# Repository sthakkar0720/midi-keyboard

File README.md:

# midi-keyboard
<h1>A custom MIDI keypad with slides, switches, rotary encoders, and capacitive touch. Built with the Hack Club Half Life guide.</h1>
I chose to make this because it is a music device and that is cool and it is one more cool piece of tech to put on my desk by my laptop. It provides accessibility for mixing my own music and I am hoping it works with spotify!

## I will be funding this project myself! This is NOT incomplete.

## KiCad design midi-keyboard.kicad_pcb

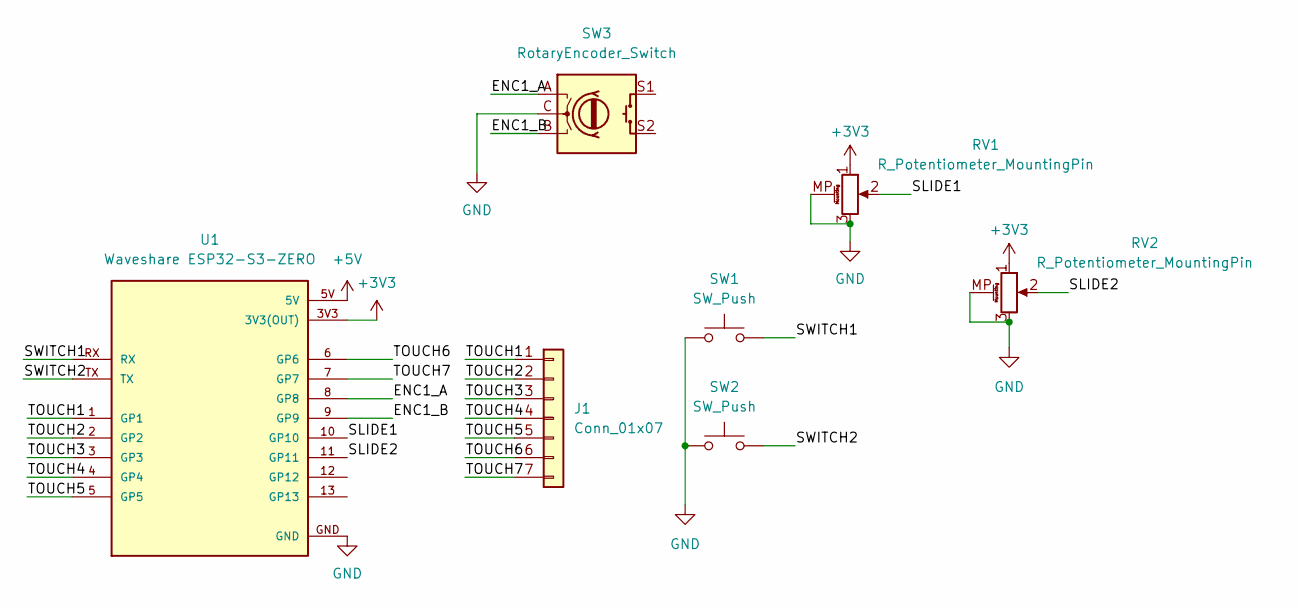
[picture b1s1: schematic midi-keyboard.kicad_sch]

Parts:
J1: Conn_01x07; Capacitative_7_Touch
RV1, RV2: R_Potentiometer_MountingPin; Potentiometer_Bourns_PTA1543_Single_Slide
SW1, SW2: SW_Push; Kailh Choc Low-Profile Switches
SW3: RotaryEncoder_Switch; RotaryEncoder_Alps_EC11E-Switch_Vertical_H20mm
U1: Waveshare ESP32-S3-ZERO; Waveshare ESP32-S3-Zero; PARTREV NA

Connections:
+3V3: RV1.1, RV2.1, U1.3V3 (3V3(OUT))
+5V: U1.5V
/ENC1_A: SW3.A, U1.8 (GP8)
/ENC1_B: SW3.B, U1.9 (GP9)
/SLIDE1: RV1.2, U1.10 (GP10)
/SLIDE2: RV2.2, U1.11 (GP11)
/SWITCH1: SW1.2, U1.RX
/SWITCH2: SW2.2, U1.TX
/TOUCH1: J1.1, U1.1 (GP1)
/TOUCH2: J1.2, U1.2 (GP2)
/TOUCH3: J1.3, U1.3 (GP3)
/TOUCH4: J1.4, U1.4 (GP4)
/TOUCH5: J1.5, U1.5 (GP5)
/TOUCH6: J1.6, U1.6 (GP6)
/TOUCH7: J1.7, U1.7 (GP7)
GND: RV1.3, RV1.MP (MountPin), RV2.3, RV2.MP (MountPin), SW1.1, SW2.1, SW3.C, U1.GND

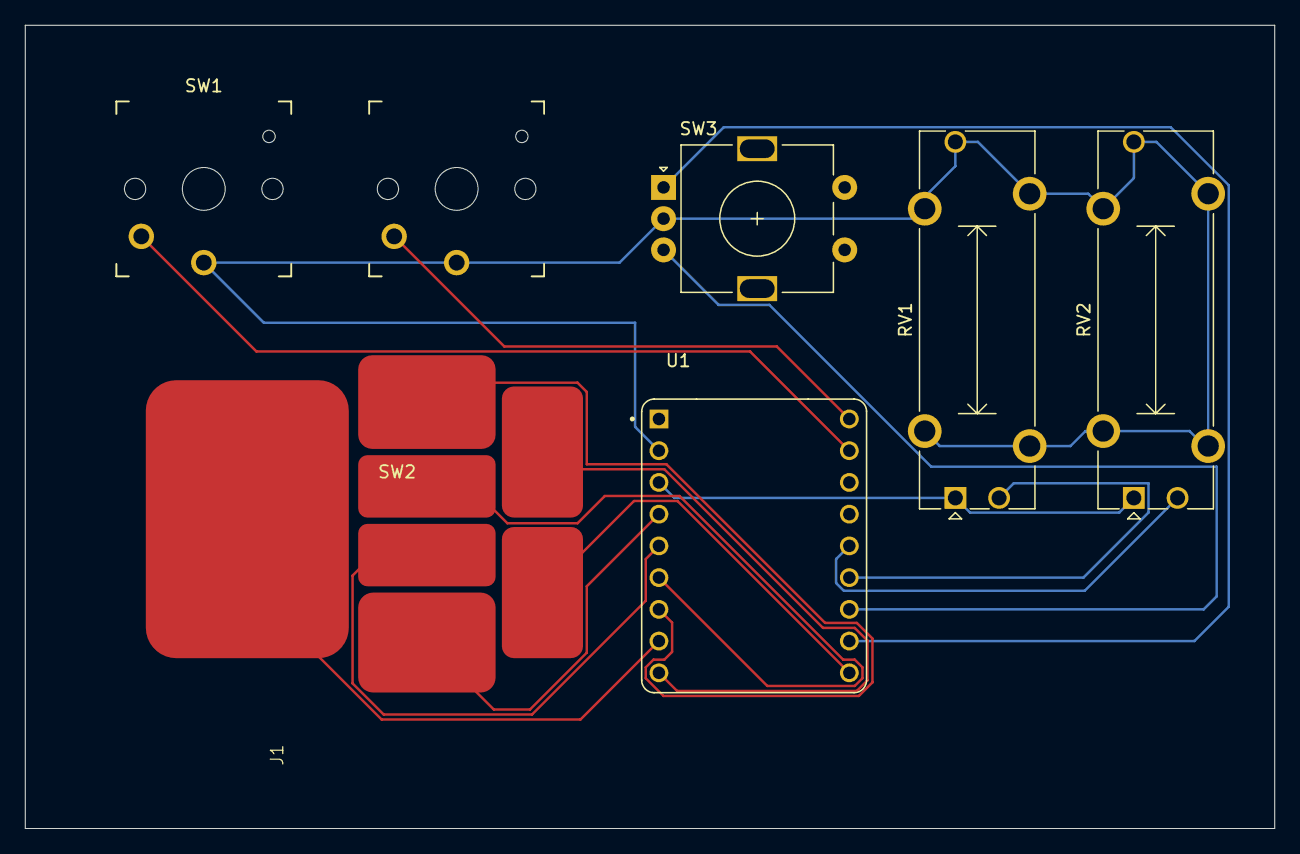
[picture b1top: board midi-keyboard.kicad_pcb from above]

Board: 2 copper layers, 100.0 x 64.3 mm, 7 parts (0 on the bottom side), 15 nets.
